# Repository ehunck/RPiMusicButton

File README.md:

# RPiMusicButton

This is a quick PCB made for a simple RPi project.  The goal is to play an audio file from a button press. One Button, one audio track, mono output,... it is very simple, quick, cheap project.

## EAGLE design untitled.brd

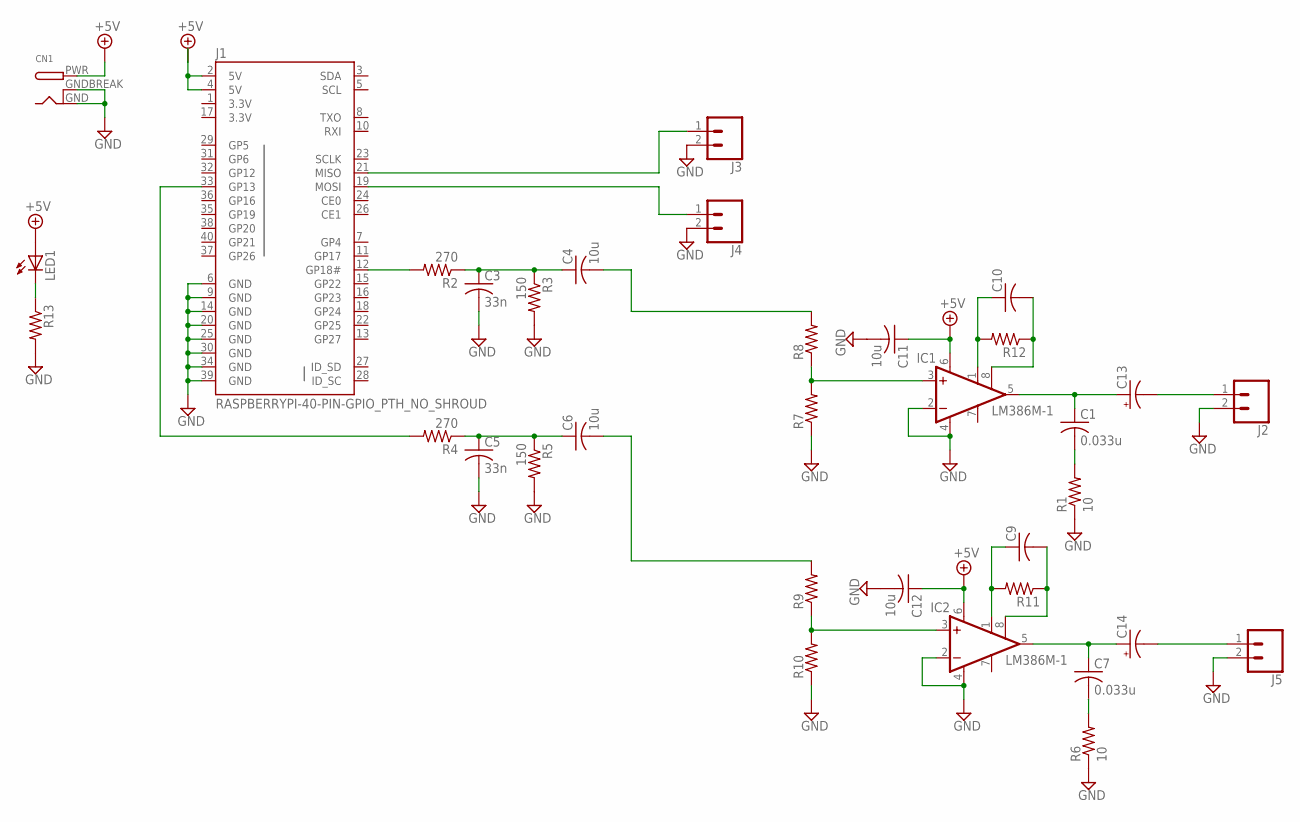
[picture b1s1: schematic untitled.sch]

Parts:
C1, C7: 0.033u; C0805
C3, C5: 33n; C0805
C4, C6, C11, C12: 10u; C0805
C9, C10: C-USC0805; C0805
C13, C14: CPOL-USD; PANASONIC_D
CN1: DCBARRELPTH; DCJACK_2MM_PTH
IC1, IC2: LM386M-1; SO08
J1: RASPBERRYPI-40-PIN-GPIO_PTH_NO_SHROUD; 2X20
J2, J3, J4, J5: CONN_02; 1X02
LED1: LEDCHIP-LED0805; CHIP-LED0805
R1, R6: 10; R0805
R2, R4: 270; R0805
R3, R5: 150; R0805
R7, R8, R9, R10, R11, R12, R13: R-US_R0805; R0805

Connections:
3.3V: J1.1 (3.3V), J1.17 (3.3V)
+5V: C11.1, C12.1, CN1.PWR, IC1.6 (VS), IC2.6 (VS), J1.2 (5V), J1.4 (5V), LED1.A
AUDIO_0: C4.2, R8.2
AUDIO_1: C6.2, R9.2
GND: C3.2, C5.2, C11.2, C12.2, CN1.GND, CN1.GNDBREAK, IC1.2 (-IN), IC1.4 (GND), IC2.2 (-IN), IC2.4 (GND), J1.6 (GND), J1.9 (GND), J1.14 (GND), J1.20 (GND), J1.25 (GND), J1.30 (GND), J1.34 (GND), J1.39 (GND), J2.2, J3.2, J4.2, J5.2, R1.1, R3.2, R5.2, R6.1, R7.1, R10.1, R13.2
unnamed: C1.1, C13.+, IC1.5 (OUT)
unnamed: C1.2, R1.2
unnamed: C13.-, J2.1
unnamed: J1.21 (MISO), J3.1
unnamed: J1.19 (MOSI), J4.1
unnamed: J1.12 (GP18#), R2.2
unnamed: J1.33 (GP13), R4.2
unnamed: C3.1, C4.1, R2.1, R3.1
unnamed: C5.1, C6.1, R4.1, R5.1
unnamed: C7.1, C14.+, IC2.5 (OUT)
unnamed: C7.2, R6.2
unnamed: C14.-, J5.1
unnamed: IC2.3 (+IN), R9.1, R10.2
unnamed: IC1.3 (+IN), R7.2, R8.1
unnamed: C9.1, IC2.1 (GAIN), R11.2
unnamed: C9.2, IC2.8 (GAIN), R11.1
unnamed: C10.1, IC1.1 (GAIN), R12.2
unnamed: C10.2, IC1.8 (GAIN), R12.1
unnamed: LED1.C, R13.1

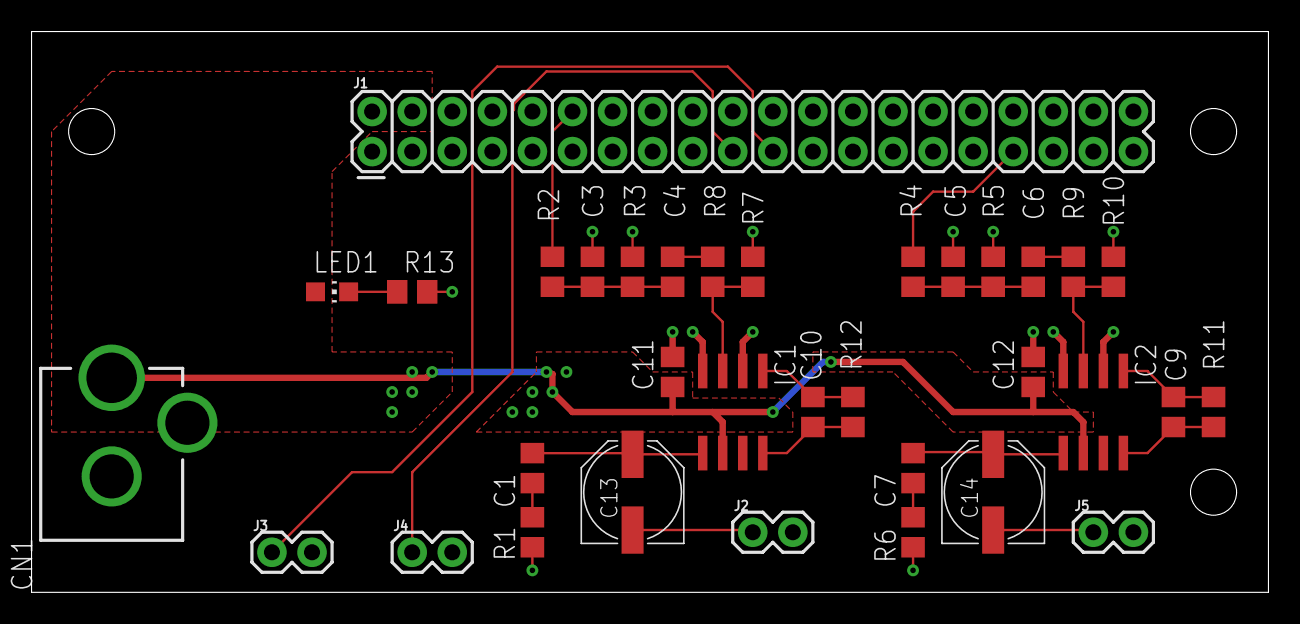
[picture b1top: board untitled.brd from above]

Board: 2 copper layers, 78.4 x 35.5 mm, 34 parts (0 on the bottom side), 24 nets.

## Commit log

2019-04-05 - Added RPi board files with audio output

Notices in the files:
parts and their libraries:
SparkFun-Connectors: Licensing: Creative Commons ShareAlike 4.0 International - https://creativecommons.org/licenses/by-sa/4.0
